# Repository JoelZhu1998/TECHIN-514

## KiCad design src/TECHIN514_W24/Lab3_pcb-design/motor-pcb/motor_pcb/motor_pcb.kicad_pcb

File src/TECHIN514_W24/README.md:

# TECHIN514_W24
Labs and Assignments for TECHIN514 W24

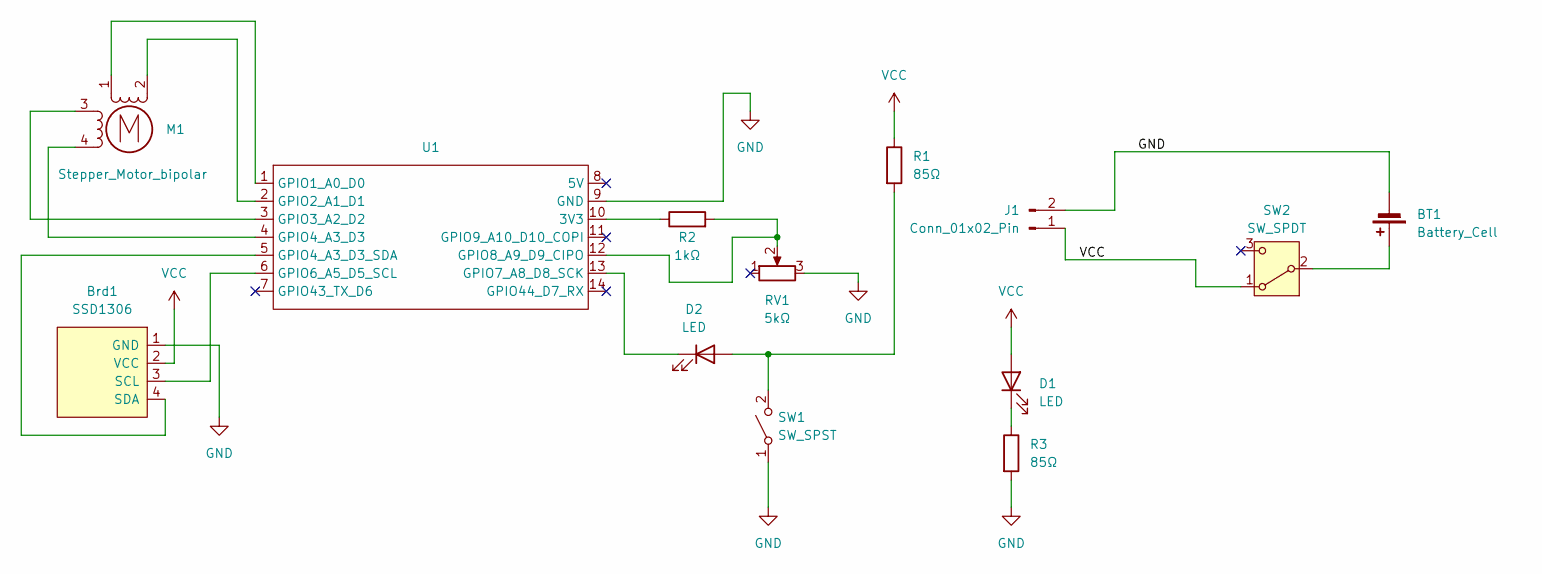
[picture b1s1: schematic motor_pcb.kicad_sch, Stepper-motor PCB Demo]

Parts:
BT1: Battery_Cell; JST_NV_B02P-NV_1x02_P5.00mm_Vertical
Brd1: SSD1306; 128x64OLED
D1, D2: LED; LED_0805_2012Metric_Pad1.15x1.40mm_HandSolder
J1: Conn_01x02_Pin; JST_NV_B02P-NV_1x02_P5.00mm_Vertical
M1: Stepper_Motor_bipolar; x27_stepper
R1, R3: 85Ω; R_0805_2012Metric_Pad1.20x1.40mm_HandSolder
R2: 1kΩ; R_0805_2012Metric_Pad1.20x1.40mm_HandSolder
RV1: 5kΩ; Potentiometer_Piher_T-16H_Single_Horizontal
SW1: SW_SPST; SW_PUSH-12mm
SW2: SW_SPDT; PinHeader_1x03_P2.54mm_Vertical
U1: XIAO_ESP32_SENSE

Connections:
GND: BT1.2 (-), Brd1.1 (GND), J1.2, R3.2, RV1.3, SW1.1 (A), U1.9 (GND)
unnamed: BT1.1 (+), SW2.2 (B)
unnamed: Brd1.3 (SCL), U1.6 (GPIO6_A5_D5_SCL)
unnamed: Brd1.4 (SDA), U1.5 (GPIO4_A3_D3_SDA)
unnamed: D1.1 (K), R3.1
unnamed: D2.2 (A), R1.2, SW1.2 (B)
unnamed: D2.1 (K), U1.13 (GPIO7_A8_D8_SCK)
unnamed: M1.2 (-), U1.2 (GPIO2_A1_D1)
unnamed: R2.1, U1.10 (3V3)
unnamed: M1.1, U1.1 (GPIO1_A0_D0)
unnamed: M1.3, U1.3 (GPIO3_A2_D2)
unnamed: M1.4, U1.4 (GPIO4_A3_D3)
unnamed: R2.2, RV1.2, U1.12 (GPIO8_A9_D9_CIPO)
VCC: Brd1.2 (VCC), D1.2 (A), J1.1, R1.1, SW2.1 (A)

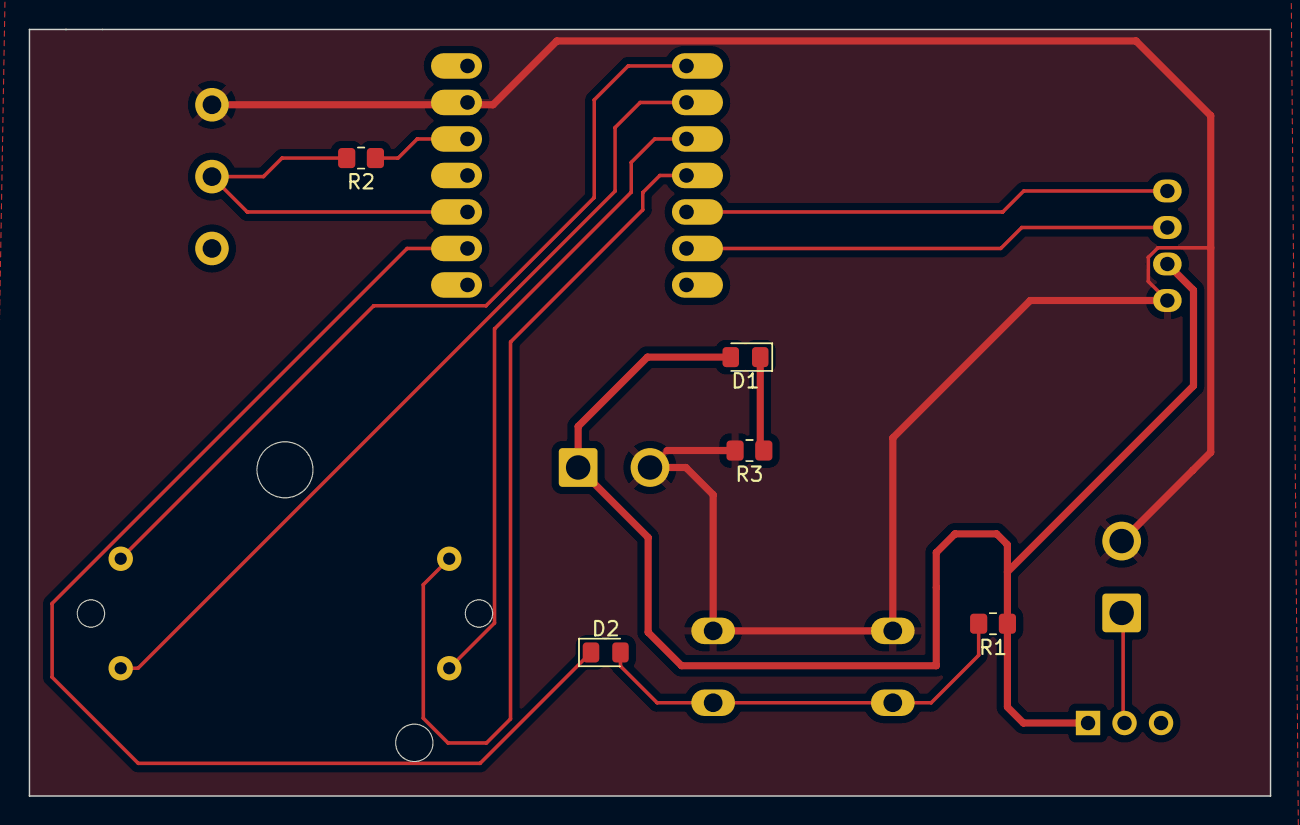
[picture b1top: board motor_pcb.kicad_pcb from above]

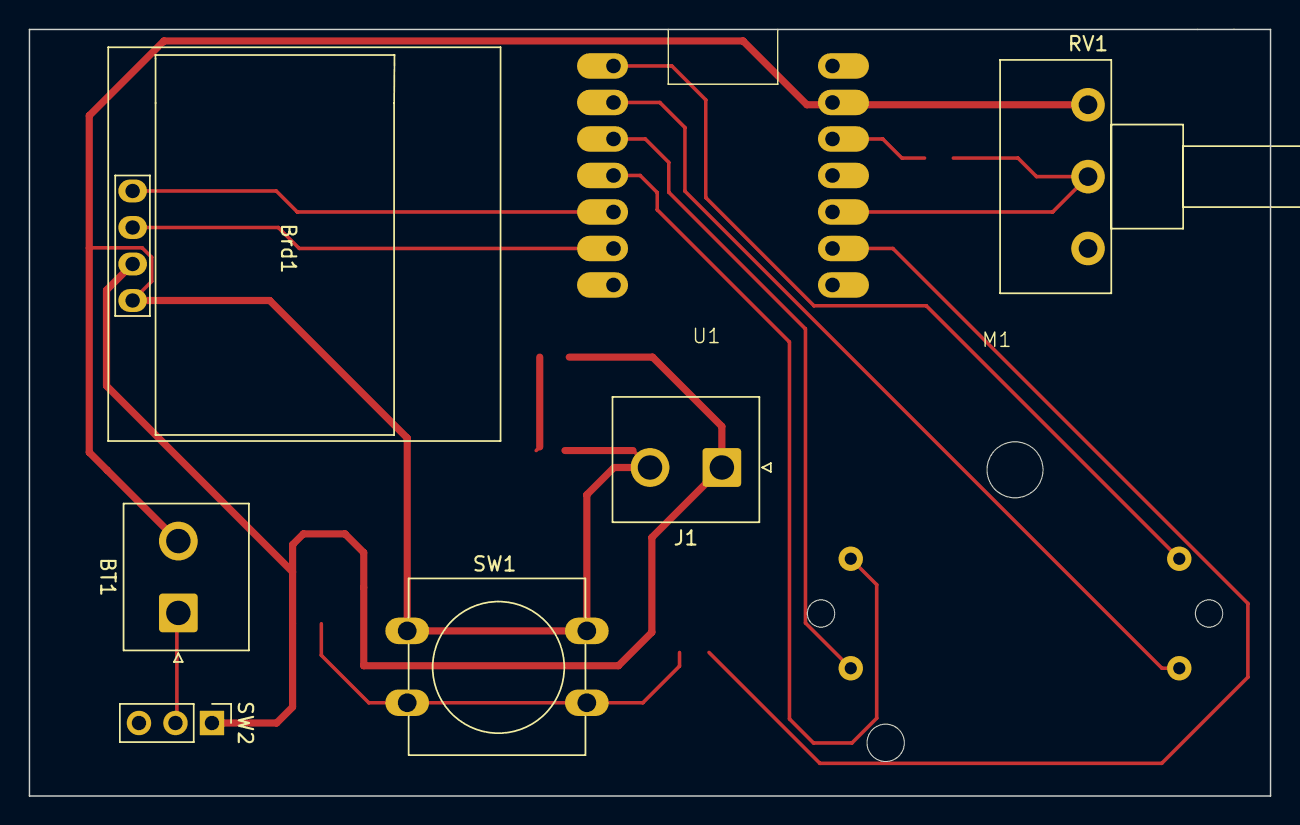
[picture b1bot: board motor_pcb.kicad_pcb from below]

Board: 2 copper layers, 86.4 x 53.3 mm, 13 parts (8 on the bottom side), 14 nets.

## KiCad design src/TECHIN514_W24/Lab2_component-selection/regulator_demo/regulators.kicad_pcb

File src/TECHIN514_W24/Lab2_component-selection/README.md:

# Lab 2 - Component selection.

## Lab Instructions

In this lab you will learn about electrical component selection and analysis, datasheet reading, and surface-mount soldering.

Follow the instruction written in[ Lab2: Component Selection.md](https://github.com/GIXLabs/TECHIN514_W24/blob/main/Lab2_component-selection/Lab2_component_selection.md) to:

* Generate the BOM spreadsheet using KiCAD;
* Reading the devices' datasheet and calculation the UNKNOWN values on the datasheet, then fill them in;
* Assemble the board with your chosen resistor values
* Verify the voltage output with the multimeter, and then attach your ESP32 to the outputs and read the voltage using an analog input pin.

**Some boards will be non-functional. Try to debug and fix it if you want. But its OK if you read zero volts to your ESP32.**

Some other resources:

* [KiCAD installation](https://www.kicad.org/download/)
* [Datasheets](https://github.com/GIXLabs/TECHIN514_W24/tree/main/Lab2_component-selection/datasheets)

## Lab Requirements

Assembling the SOT223 package circuit (on the left) is required and should be relatively easy.
Assembling the SOT23-5 package circuit (in the middle) is also required if your board has the footprints, and should be manageable.
Assembling the SC70 package (on the right) is completely optional but could be a fun challenge!

**Also there is AT LEAST ONE error in the schematic. Bonus points for finding it!**

## What to Submit on Canvas

- A single PDF file containing:
  - Your selected resistors and the calculations you made
    - Please be verbose about how you did the calculation, and what essential information you found from the datasheet
  - Screenshot of the exported BOM spreadsheet, with values filled in
  - A picture of your board
  - Link to github repo of your ESP32 code
  - Screenshot of the serial output from your ESP32 (zeros are okay if you get a non-functioning board)

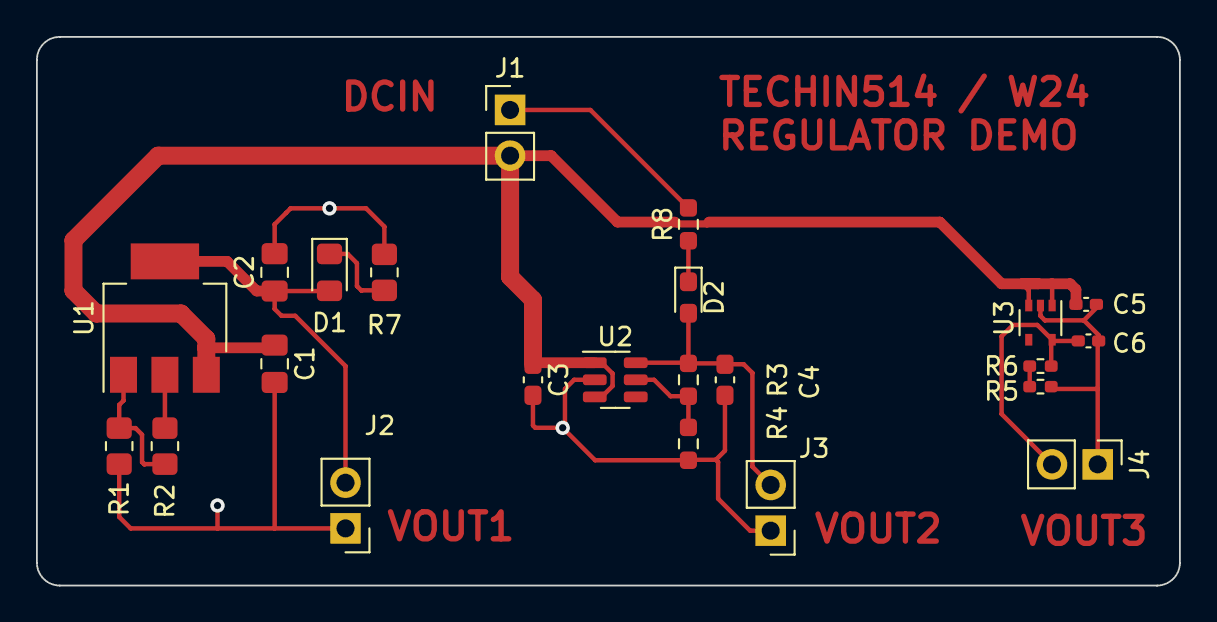
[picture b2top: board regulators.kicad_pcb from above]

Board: 2 copper layers, 63.5 x 30.5 mm, 23 parts (0 on the bottom side), 10 nets.

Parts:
C1, C2: 1uF; C_0805_2012Metric_Pad1.18x1.45mm_HandSolder
C3, C4: 1uF; C_0603_1608Metric_Pad1.08x0.95mm_HandSolder
C5, C6: 1uF; C_0402_1005Metric_Pad0.74x0.62mm_HandSolder
D1: LED; LED_0805_2012Metric_Pad1.15x1.40mm_HandSolder
D2: LED; LED_0603_1608Metric_Pad1.05x0.95mm_HandSolder
J1, J2, J3, J4: n.m.; PinHeader_1x02_P2.54mm_Vertical
R1, R2, R7: R; R_0805_2012Metric_Pad1.20x1.40mm_HandSolder
R3, R4, R8: R; R_0603_1608Metric_Pad0.98x0.95mm_HandSolder
R5, R6: R; R_0402_1005Metric_Pad0.72x0.64mm_HandSolder
U1: LM317_SOT-223; SOT-223-3_TabPin2
U2: TPS79301-EP; SOT-23-6
U3: MIC5366-3.3YC5; SOT-353_SC-70-5

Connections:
+VDC: C1.1, C3.1, C5.2, J1.2, U1.3 (VI), U2.1 (IN), U2.3 (EN), U3.1 (VIN), U3.3 (EN)
GND: C1.2, C2.2, C3.2, C4.2, C5.1, C6.2, J1.1, J2.1, J3.1, J4.1, R1.2, R4.2, R6.2, R7.2, R8.2, U2.2 (GND), U3.2 (GND)
unnamed: C2.1, D1.2 (A), J2.2, R2.2, U1.2 (VO)
unnamed: D1.1 (K), R7.1
unnamed: C4.1, D2.2 (A), J3.2, R3.1, U2.6 (OUT)
unnamed: D2.1 (K), R8.1
unnamed: C6.1, J4.2, R5.1, U3.5 (VOUT)
unnamed: R5.2, R6.1
unnamed: R1.1, R2.1, U1.1 (ADJ)
unnamed: R3.2, R4.1, U2.5 (FB)

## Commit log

2024-01-16 Rename Sketch 2.jpg to Sketch_2.jpg
2024-01-17 Create ESP32
2024-01-18 Create Final
2024-01-18 Rename
2024-01-18 Create Kicad
2024-02-07 Create BATTERY_LAB
2024-02-07 Create Strategy
2024-02-21 Create Second_Device_Code
